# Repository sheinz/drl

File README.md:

drl
===

Daytime running lamp controller. Use standard high beam lamps with reduced power to implemen daytime running lamps.
The controller is implemented using ATMEL ATTiny13A microcontroller.
It uses PWM to control lamp brightness. 

**Features:**
- Use PWM to control hi beam lamp power.
- Automatically turns on after engine is started. Detects voltage increase to determine if engine is running.
- Automatically turns off when low beam lamps is on.
- Provides DRL brightness configuration by clicking a switch. Each click slightly increases brightness.
- The brightness of the DRL is stored in EEPROM. 
- Can be completely disabled by configurin brightness that equal zero.
- If a device is malfunctioning it records errors and blinks hi beam lamps at start. 
- The error count is cleared after clicking a switch.

**Build**

In order to build the source code the following packages should be installed:

    sudo apt-get install gcc-avr
    sudo apt-get install avr-libc
    sudo apt-get install cmake
    
If you encounter errors like these:
    
    ld: crttn13a.o: No such file: No such file or directory
    undefined reference to `__eerd_byte_tn13a'
    
Copy libraries crttn13a.o and libc.a into tiny-stack subdirectory:

    sudo cp /usr/lib/avr/lib/avr25/crttn13a.o /usr/lib/avr/lib/avr25/tiny-stack/
    sudo cp /usr/lib/avr/lib/avr25/libc.a /usr/lib/avr/lib/avr25/tiny-stack/
    
To build and upload the firmware:
    
    mkdir drl-build
    cd drl-build
    cmake ../drl
    make
    make upload

--------------

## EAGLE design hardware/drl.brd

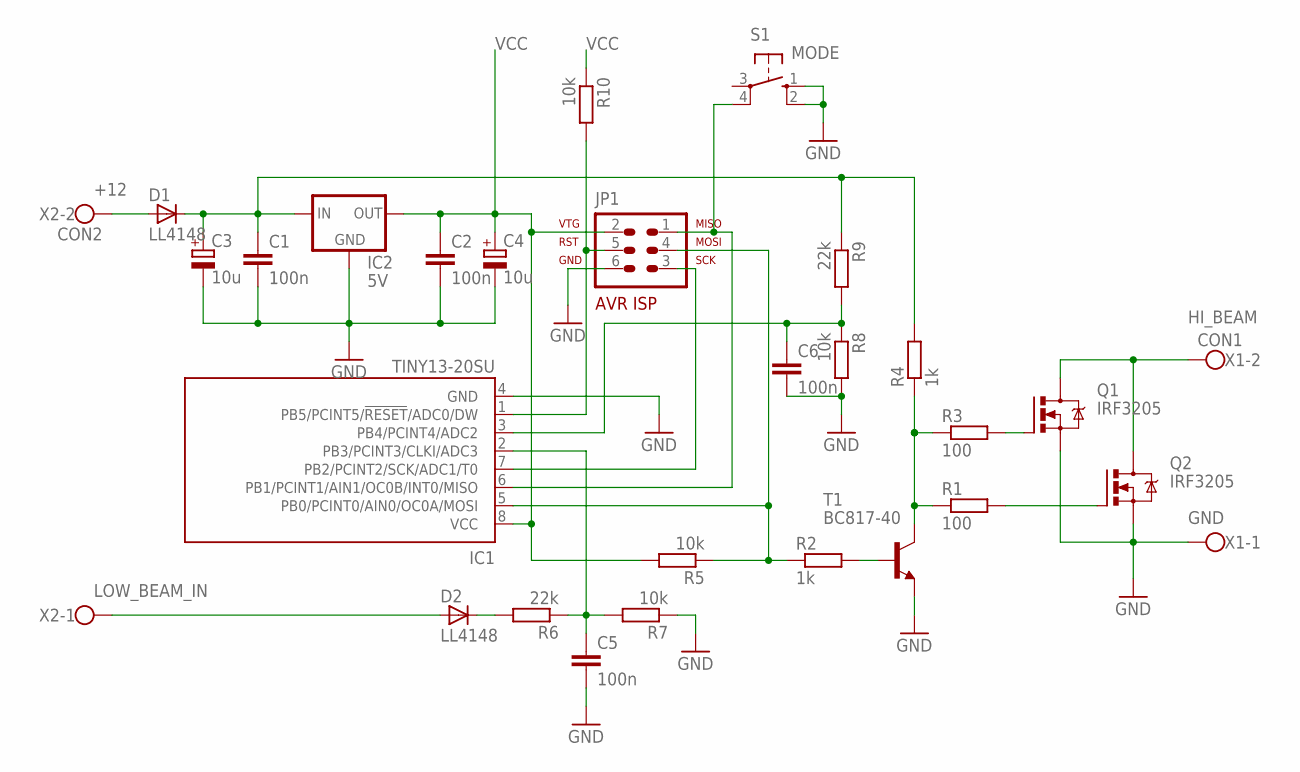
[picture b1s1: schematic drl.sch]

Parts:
C1, C2, C5, C6: 100n; C0805K
C3, C4: 10u; SMC_D
D1, D2: LL4148; SOD80
IC1: TINY13-20SU; 8S2
IC2: 5V; SOIC8
JP1: AVR-ISP-6
Q1, Q2: IRF3205; TO220BV
R1, R3: 100; R0805
R2: 1k; 0204/7
R4: 1k; R0805
R5, R7, R8, R10: 10k; R0805
R6, R9: 22k; R0805
S1: MODE; B3F-10XX
T1: BC817-40; SOT23-BEC
X1: CON1; W237-102
X2: CON2; W237-102

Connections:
+12: D1.2 (A), X2.2
GND: C1.2, C2.2, C3.-, C4.-, C5.2, C6.2, IC1.4 (GND), IC2.2 (GND), IC2.3 (GND), IC2.6 (GND), IC2.7 (GND), JP1.6, Q1.S, Q2.S, R7.1, R8.2, S1.1 (S), S1.2 (S1), T1.E, X1.1
HI_BEAM: Q1.D, Q2.D, X1.2
LOW_BEAM_IN: D2.2 (A), X2.1
unnamed: Q2.G, R1.2
unnamed: D2.1 (C), R6.2
unnamed: Q1.G, R3.2
unnamed: IC1.7 (PB2/PCINT2/SCK/ADC1/T0), JP1.3
unnamed: R2.2, T1.B
unnamed: R1.1, R3.1, R4.1, T1.C
unnamed: C5.1, IC1.2 (PB3/PCINT3/CLKI/ADC3), R6.1, R7.2
unnamed: IC1.1 (PB5/PCINT5/!RESET!/ADC0/DW), JP1.5, R10.2
unnamed: IC1.5 (PB0/PCINT0/AIN0/OC0A/MOSI), JP1.4, R2.1, R5.1
unnamed: IC1.6 (PB1/PCINT1/AIN1/OC0B/INT0/MISO), JP1.1, S1.4 (P1)
unnamed: C6.1, IC1.3 (PB4/PCINT4/ADC2), R8.1, R9.2
VCC: C2.1, C4.+, IC1.8 (VCC), IC2.1 (OUT), JP1.2, R5.2, R10.1
VCC12: C1.1, C3.+, D1.1 (C), IC2.8 (IN), R4.2, R9.1

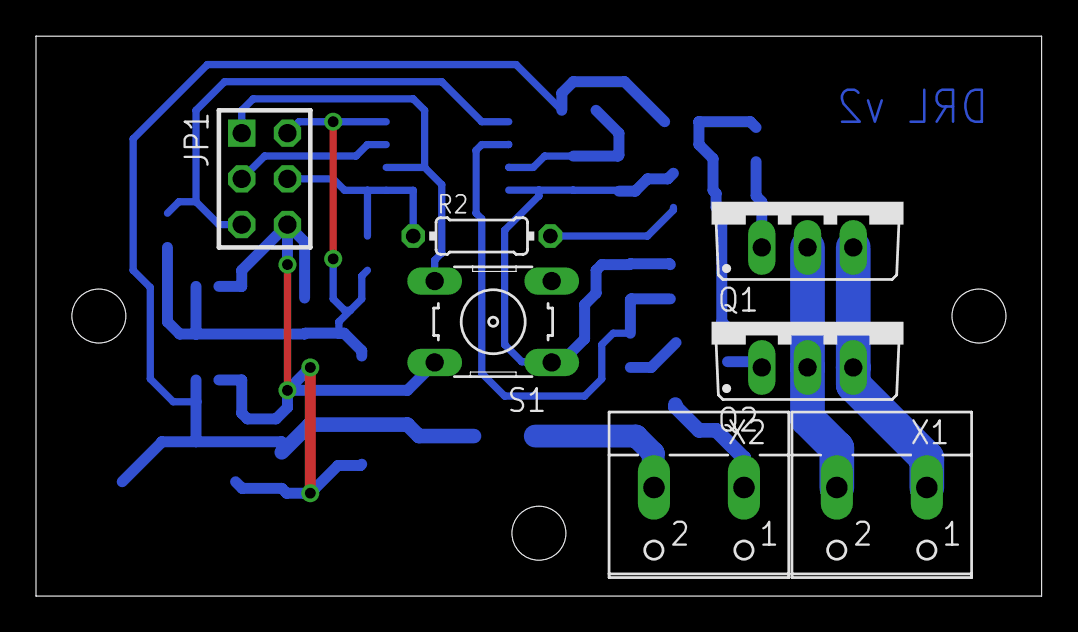
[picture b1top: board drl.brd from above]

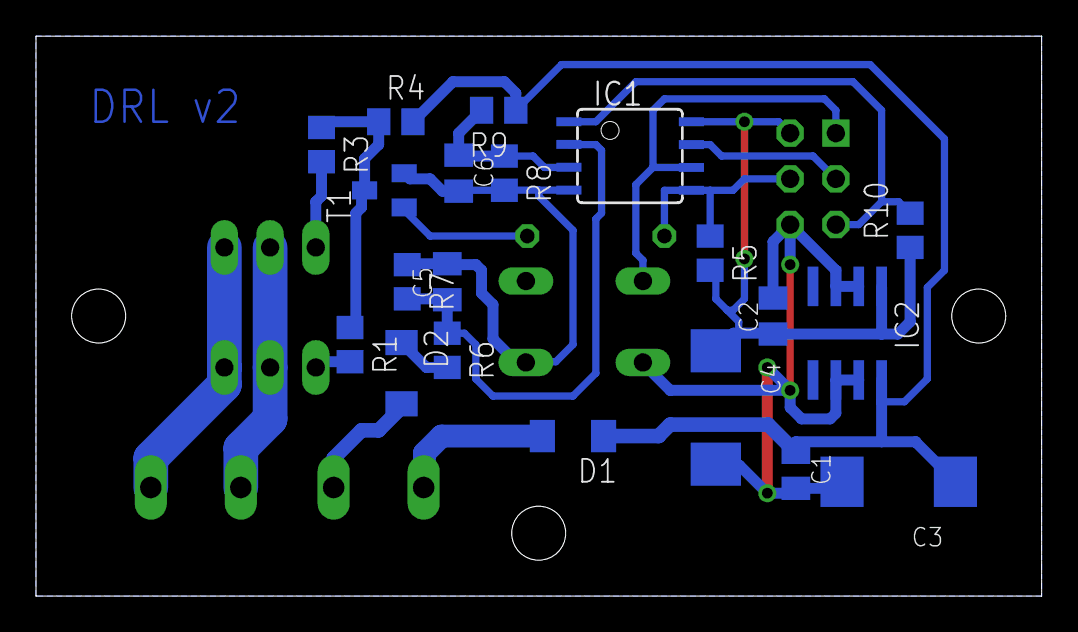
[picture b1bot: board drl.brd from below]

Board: 2 copper layers, 55.9 x 31.1 mm, 27 parts (20 on the bottom side), 17 nets.

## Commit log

2013-09-09 Initial schematic and board design
2013-09-09 Made the board slightly shorter. More compact component placement.
2013-09-09 Added ground plane
2013-09-11 Initial draft version of the source code for drl
2013-09-14 Added draft implementation of pwm
2013-09-14 Change in schematic and board.
2013-09-14 Saving PWM into EEPROM
2013-09-14 Resistor value was edited
2013-09-14 Write eeprom while flashing
2013-09-14 Add watch dog timer and error indication at power on
2013-09-19 Second version of hardware (schematic and pcb)
2013-09-19 Add a library with extra components what is missing in Eagle standard library.
2013-09-19 Small editions in schematic and board design.
2013-09-19 The dimentions were adjusted to fit the case
2013-09-21 New version. Added switch support. Turn on when engine is started measuring voltage
2013-09-21 Added pictures of the device
2013-09-21 Resized pictures
2013-09-21 Add schematic and pcb as images
2013-09-21 Removed unused CMakeLists.txt
2013-10-13 Switched to CMake build system
2013-10-13 Fix for avrdude info command
2016-10-19 Create gh-pages branch via GitHub
